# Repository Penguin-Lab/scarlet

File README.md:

# scarlet
A Scarlet é uma hexapod desenvolvida na disciplina de Robôs a Patas para andar de forma autônoma ou para ser controlada pelo celular. Para se locomover, ela possui 6 patas de 3 graus de liberdade cada (3 motores) e uma ESP32 que comanda o conjunto! Ela é a nossa viúva negra, a irmã da Tiffany e a nova integrante robótica do nosso espaço inteligente!

# Estrutura física
A estrutura física do robô é composta por seis patas de três eixos cada (três motores). As patas são fixadas a duas placas de PLA para deixar o robô firme. As peças são todas projetadas em 3D e foram impressas utilizando PLA, podendo ser encontradas na pasta Pecas_3d deste projeto.

## Peças 3D em STL
As peças em 3D desenvolvidas para este projeto foram baseadas no projeto da hexapod Tiffany. Na pasta Pecas_3d, estão listadas essas peças em STL. Para ajudar, segue abaixo uma lista de todas as peças que devem ser impressas e qual o valor da sua maior dimensão (para ajudar na escolha da impressora):
* Corpo
  * 1x [SCARLET_BODY_DOWN.STL (230 mm)](https://github.com/Penguin-Lab/scarlet/blob/main/Pecas_3d/SCARLET_BODY_DOWN.STL)
  * 1x [SCARLET_BODY_UP.STL (230 mm)](https://github.com/Penguin-Lab/scarlet/blob/main/Pecas_3d/SCARLET_BODY_UP.STL)
  * 4x [SCARLET_SPACER.STL (68 mm)](https://github.com/Penguin-Lab/scarlet/blob/main/Pecas_3d/SCARLET_SPACER.STL)
  * 2x [SCARLET_SPACER_FRONT.STL (68 mm)](https://github.com/Penguin-Lab/scarlet/blob/main/Pecas_3d/SCARLET_SPACER_FRONT.STL)
  * 1x [SCARLET_SUPPORT_PCI.STL (120 mm)](https://github.com/Penguin-Lab/scarlet/blob/main/Pecas_3d/SCARLET_SUPPORT_PCI.STL)
  * 1x [SCARLET_SUPPORT_SWITCH.STL (50 mm)](https://github.com/Penguin-Lab/scarlet/blob/main/Pecas_3d/SCARLET_SUPPORT_SWITCH.STL)
  * 1x [SCARLET_SYMBOL.STL (50 mm)](https://github.com/Penguin-Lab/scarlet/blob/main/Pecas_3d/SCARLET_SYMBOL.STL)
  * 1x [SCARLET_LOGO.STL (50 mm)](https://github.com/Penguin-Lab/scarlet/blob/main/Pecas_3d/SCARLET_LOGO.STL)
* Patas
  * 6x [SCARLET_TIBIA_LEFT.STL (141 mm)](https://github.com/Penguin-Lab/scarlet/blob/main/Pecas_3d/SCARLET_TIBIA_LEFT.STL)
  * 6x [SCARLET_TIBIA_LEFT.STL espelhado (141 mm)](https://github.com/Penguin-Lab/scarlet/blob/main/Pecas_3d/SCARLET_TIBIA_LEFT.STL)
  * 6x [SCARLET_TIBIA_MIDDLE.STL (63 mm)](https://github.com/Penguin-Lab/scarlet/blob/main/Pecas_3d/SCARLET_TIBIA_MIDDLE.STL)
  * 3x [SCARLET_SHIELD_A.STL (10 mm)](https://github.com/Penguin-Lab/scarlet/blob/main/Pecas_3d/SCARLET_SHIELD_A.STL)
  * 3x [SCARLET_SHIELD_A.STL espelhado (10 mm)](https://github.com/Penguin-Lab/scarlet/blob/main/Pecas_3d/SCARLET_SHIELD_A.STL)
  * 3x [SCARLET_SHIELD_B.STL (10 mm)](https://github.com/Penguin-Lab/scarlet/blob/main/Pecas_3d/SCARLET_SHIELD_B.STL)
  * 3x [SCARLET_SHIELD_B.STL espelhado (10 mm)](https://github.com/Penguin-Lab/scarlet/blob/main/Pecas_3d/SCARLET_SHIELD_B.STL)
  * 3x [SCARLET_FEMUR_FRONT.STL (110 mm)](https://github.com/Penguin-Lab/scarlet/blob/main/Pecas_3d/SCARLET_FEMUR_FRONT.STL)
  * 3x [SCARLET_FEMUR_BACK.STL (118 mm)](https://github.com/Penguin-Lab/scarlet/blob/main/Pecas_3d/SCARLET_FEMUR_BACK.STL)
  * 3x [SCARLET_FEMUR_FRONT.STL espelhado (110 mm)](https://github.com/Penguin-Lab/scarlet/blob/main/Pecas_3d/SCARLET_FEMUR_FRONT.STL)
  * 3x [SCARLET_FEMUR_BACK.STL espelhado (118 mm)](https://github.com/Penguin-Lab/scarlet/blob/main/Pecas_3d/SCARLET_FEMUR_BACK.STL)
  * 6x [SCARLET_FEMUR_MIDDLE.STL (51 mm)](https://github.com/Penguin-Lab/scarlet/blob/main/Pecas_3d/SCARLET_FEMUR_MIDDLE.STL)
  * 6x [SCARLET_OMBRO_UP.STL (61 mm)](https://github.com/Penguin-Lab/scarlet/blob/main/Pecas_3d/SCARLET_OMBRO_UP.STL)
  * 3x [SCARLET_OMBRO_DOWN_LEFT.STL (61 mm)](https://github.com/Penguin-Lab/scarlet/blob/main/Pecas_3d/SCARLET_OMBRO_DOWN_LEFT.STL)
  * 3x [SCARLET_OMBRO_DOWN_LEFT.STL espelhado (61 mm)](https://github.com/Penguin-Lab/scarlet/blob/main/Pecas_3d/SCARLET_OMBRO_DOWN_LEFT.STL)
* Motor
  * 12x [SCARLET_TAMPA_MOTOR_DS3230.STL (41 mm)](https://github.com/Penguin-Lab/scarlet/blob/main/Pecas_3d/SCARLET_TAMPA_MOTOR_DS3230.STL)

Obs 1: a tampa de 12 motores deverão ser trocadas pelas peças [SCARLET_TAMPA_MOTOR_DS3230.STL](https://github.com/Penguin-Lab/scarlet/blob/main/Pecas_3d/SCARLET_TAMPA_MOTOR_DS3230.STL) para que seja possível fixar os rolamentos nas patas. Serão utilizados 3 rolamentos por pata.

Obs 2: os motores ficam fixados nas peças por [discos metálicos pequenos padrão para eixos de servo](https://a.aliexpress.com/_mPHt3nf).

## Outros itens da estrutura
Alguns outros itens são necessários para finalizar a estrutura da Tiffany:
* 6x Parafusos m4 ou similar de cm, arruelas e porcas auto-travantes: prender as peças [SCARLET_BODY_UP.STL](https://github.com/Penguin-Lab/scarlet/blob/main/Pecas_3d/SCARLET_BODY_UP.STL) e [SCARLET_BODY_DOWN.STL](https://github.com/Penguin-Lab/scarlet/blob/main/Pecas_3d/SCARLET_BODY_DOWN.STL)
* 12x Parafusos m4 de 5 cm: prender as peças [SCARLET_OMBRO_DOWN_LEFT.STL](https://github.com/Penguin-Lab/scarlet/blob/main/Pecas_3d/SCARLET_OMBRO_DOWN_LEFT.STL) e [SCARLET_OMBRO_UP.STL](https://github.com/Penguin-Lab/scarlet/blob/main/Pecas_3d/SCARLET_OMBRO_UP.STL)
* 24x Parafusos m4 de 5,5 cm: prender as peças [SCARLET_OMBRO_DOWN_LEFT.STL](https://github.com/Penguin-Lab/scarlet/blob/main/Pecas_3d/SCARLET_OMBRO_DOWN_LEFT.STL) e [SCARLET_OMBRO_UP.STL](https://github.com/Penguin-Lab/scarlet/blob/main/Pecas_3d/SCARLET_OMBRO_UP.STL)
* Parafusos m3 de cm: prender todas as peças das patas e a [SCARLET_SUPORT_PCI.STL](https://github.com/Penguin-Lab/scarlet/blob/main/Pecas_3d/SCARLET_SUPORT_PCI.STL) no corpo do robô e na placa
* 6x Tiras de EVA de 5mm: colar e prender com braçadeira na ponta das peças [SCARLET_SHIELD_A.STL](https://github.com/Penguin-Lab/scarlet/blob/main/Pecas_3d/SCARLET_SHIELD_A.STL) e [SCARLET_SHIELD_B.STL](https://github.com/Penguin-Lab/scarlet/blob/main/Pecas_3d/SCARLET_SHIELD_B.STL) para evitar que o robô deslize

## Placa de circuito impresso
No projeto, foi desenvolvida uma placa de circuito para servir como shield para a ESP32 e conexão com as duas placas PCA9685 e com futuros sensores e displays I2C.

## Calibração dos motores
A calibração dos motores é feita utilizando o [CALIBRADOR DE MOTORES](https://github.com/Penguin-Lab/calib_servomotor) conectado às PCAs da Scarlet. Isso deve ser feito pelo clock das PCAs ser diferente de uma placa para outra. Logo, os motores da esquerda são calibrados utilizando a PCA da esquerda e os da direita com a PCA da direita. Os valores retornados pela calibração são jogados nesta [PLANILHA](https://docs.google.com/spreadsheets/d/1Kh9AVbb79lXnJq5dlCiB7NEVVmcJWRX6X2CdDR9_QZo/edit?usp=sharing). A planilha ajeita os valores de PWM retornados na IDE do Arduino para valores que representem 0 e 180 graus dos motores já na estrutura das patas. Esses valores são os mesmos listados no código de comando da Scarlet.

## Componentes eletrônicos
Os componentes eletrônicos embarcados no robô e equipamentos utilizados são:
* Controlador com Wi-fi e Bluetooth
  * 1x ESP32 (38 pinos)
* Motores
  * 18x Servo DS3230 PRO-180
* 2x Placas PCA9685 para comando dos 18 motores
* Chave (switch)
* Alimentação
  * Bateria Zippy LiFe 1100mAh 2s 6,6V (ESP32)
  * Bateria TM Hobbies LiFe 2100mAh 2s 6,6v (motores)

# Software
Na pasta de códigos, há um código de programação da ESP32 (38 pinos). Ele é um exemplo em C++ do comando de movimentação da Tiffany:
* Dabble: a ESP32 pode se comunicar com o aplicativo Dabble no celular e receber comandos de ação.

## Alunos participantes e desenvolvedores da Scarlet
* Állefe Amorim Florindo
* Eduarda Ferreira Cipriano
* Gustavo Assis Ferreira
* Joab Felippe de Souza Lima
* João Pedro Queiroz dos Santos
* Junior Guimarães de Oliveira
* Luis Philipe Zioto de Barros
* Rafaela da Silva Crise
* Ricardo dos Santos Barros
* Samuel Gurgel Rocha

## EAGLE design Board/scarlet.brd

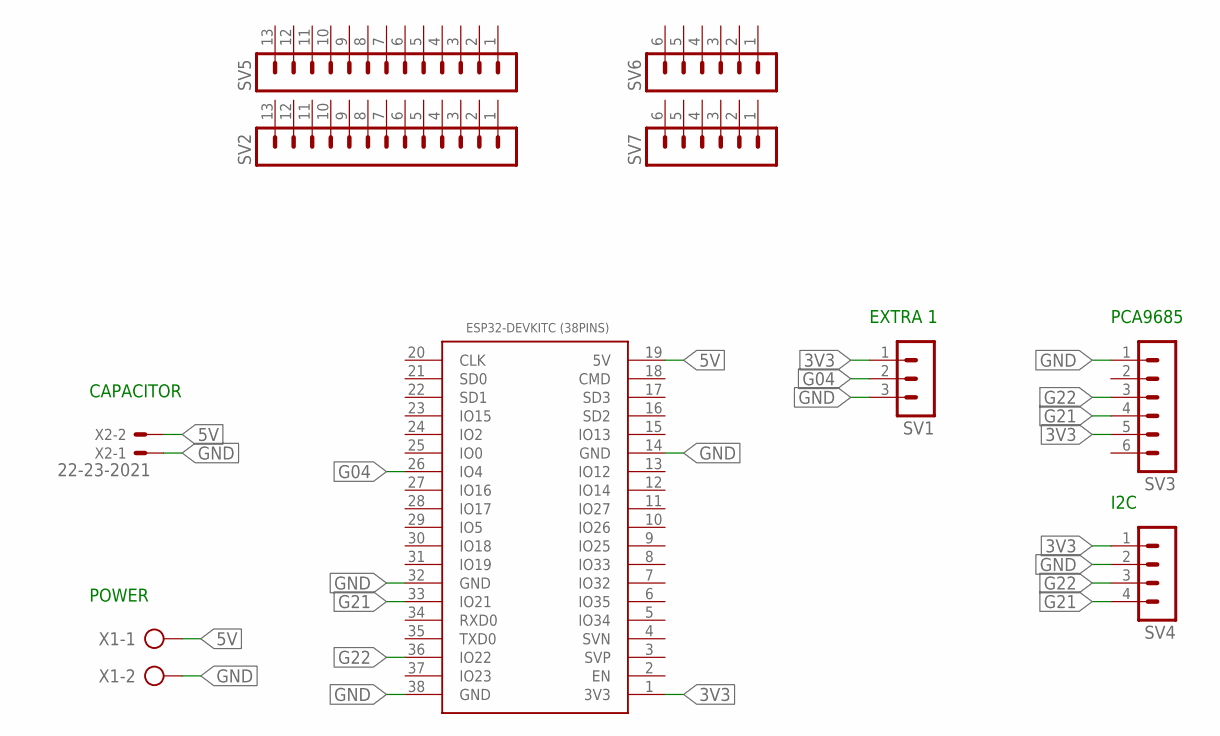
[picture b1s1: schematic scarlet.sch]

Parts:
ESP32-DEVKITC(38PINS)1: ESP32DEVKITC_38PINS; ESP32-DEVKITC
SV1: MA03-1
SV2, SV5: MA13-1
SV3, SV6, SV7: MA06-1
SV4: MA04-1
X1: AK300/2
X2: 22-23-2021

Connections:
3V3: ESP32-DEVKITC(38PINS)1.1 (3V3), SV1.1, SV3.5, SV4.1
5V: ESP32-DEVKITC(38PINS)1.19 (5V), X1.1, X2.2
G04: ESP32-DEVKITC(38PINS)1.26 (IO4), SV1.2
G21: ESP32-DEVKITC(38PINS)1.33 (IO21), SV3.4, SV4.4
G22: ESP32-DEVKITC(38PINS)1.36 (IO22), SV3.3, SV4.3
GND: ESP32-DEVKITC(38PINS)1.14 (GND), ESP32-DEVKITC(38PINS)1.32 (GND), ESP32-DEVKITC(38PINS)1.38 (GND), SV1.3, SV3.1, SV4.2, X1.2, X2.1

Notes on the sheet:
CAPACITOR
POWER
EXTRA 1
PCA9685
I2C

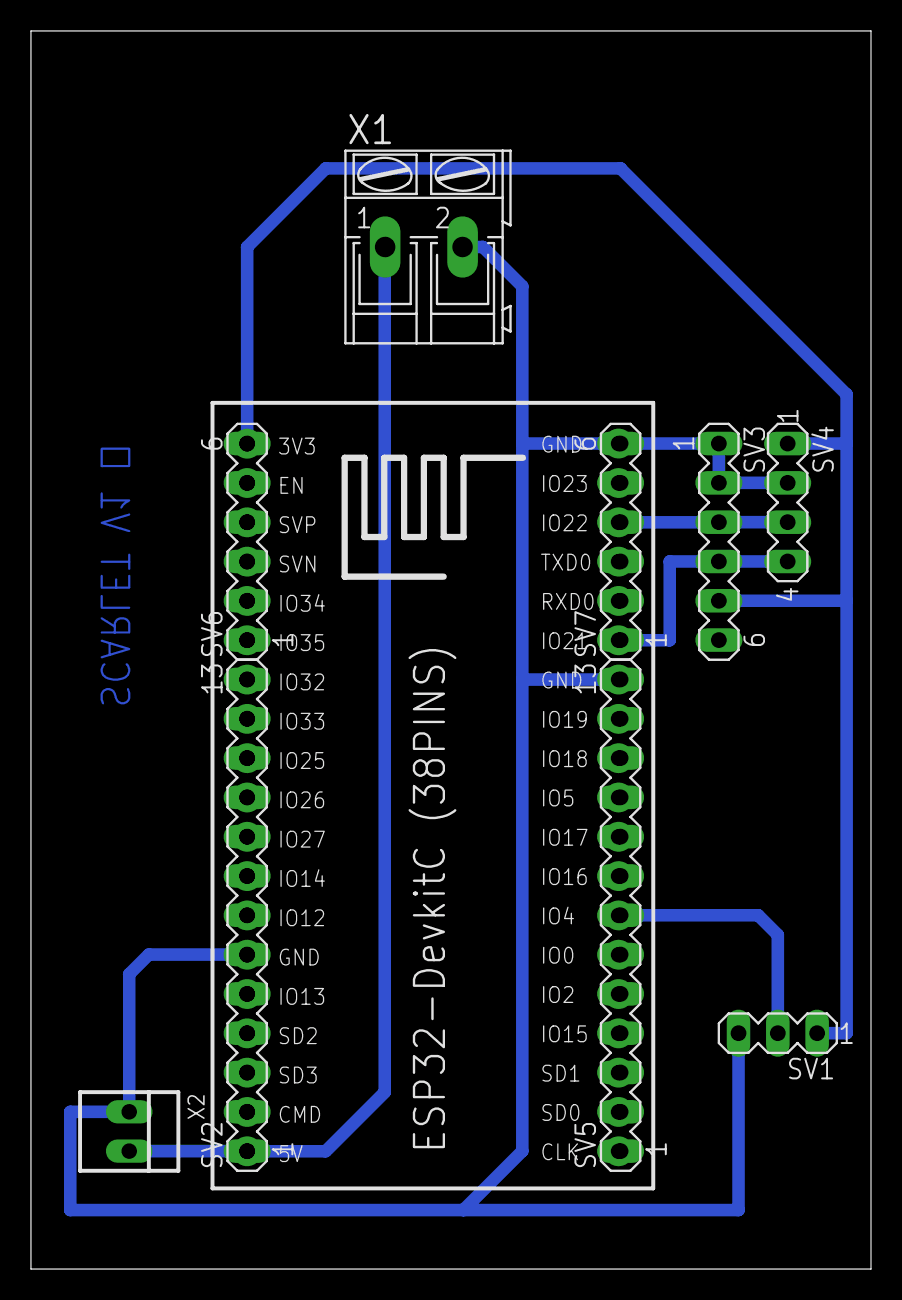
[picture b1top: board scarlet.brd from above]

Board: 2 copper layers, 54.3 x 80.0 mm, 10 parts (0 on the bottom side), 6 nets.

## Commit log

2025-08-14 Create opa
2025-10-04 Rename scarlet0.png to images/scarlet0.png
2025-10-04 Rename scarlet1.png to images/scarlet1.png
2025-10-04 Rename scarlet2.png to images/scarlet2.png
2025-10-04 Rename scarlet3.png to images/scarlet3.png
2025-10-04 Rename shield_esp_projeto.png to images/shield_esp_projeto.png
2025-10-17 Adicionado o girar parecido com o uniciclo, armar com Start 17/10/2025
    Refactor trajectory calculations and joystick handling.
2025-10-17 dar a patinha alto
2025-10-20 corrigido o calculo de P0, P1, P2 e P3
2025-10-20 Adjust TOTAL_PONTOS and delay for movement
    Reduced TOTAL_PONTOS to 25 and adjusted trajectory calculations accordingly. Increased delay in omnidirectional movement.
2025-10-22 Refactor hexapod control parameters and debug output
2025-10-23 Disable debug mode and adjust calibration values
2025-10-23 Add motor calibration section to README
    Added motor calibration section with details and links.
2025-10-30 Refactor trajectory calculations and update calibration
    Removed QUARTO_PONTOS definition and adjusted calculations in trajetoriaLinear function. Updated Pata DirT calibration values.
2025-11-10 Refactor joystick angle handling and delays
    Refactor joystick angle conversion functions and adjust delays.
2025-11-10 Modify joystick angle conversion with offset
